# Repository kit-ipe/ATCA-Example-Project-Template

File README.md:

# ATCA Template

ATCA template containing multiple sub-projects.

## Project Folder structure

- fba_template "Full FBA" - Carrier Style with debugging with KRIA SoC and Carrier according to AMC.0 Spec.
- rtm_template "Full RTM" - RTM to be used with "Full Version"
- amc_template "AMC" - AMC to be used with "Full FBA" or "Carrier FBA"
- led_pcb: LED PCB to be used with every AMC Carier

- BOM: example BOM combination for one assemby of 1 Full FBA, 1 Full RTM and 1 LED PCB and 4 AMC

## Individual Project Folder structure

- sch/ -> to store sub schematic sheets
- mech -> to store dxf files used in mechanical tasks
- images -> to store images for the README or other purposes
- gerbers -> to store Gerber files

## Repositories

- [github](https://github.com/kit-ipe/ATCA-Example-Project-Template)

## Licensing

Copyright Luis Ardila, Carsten Schmerbeck 2023.

This source describes Open Hardware and is licensed under the CERN-OHL-P v2
You may redistribute and modify this documentation and make products
using it under the terms of the CERN-OHL-P v2 [https:/cern.ch/cern-ohl](https:/cern.ch/cern-ohl).
This documentation is distributed WITHOUT ANY EXPRESS OR IMPLIED
WARRANTY, INCLUDING OF MERCHANTABILITY, SATISFACTORY QUALITY
AND FITNESS FOR A PARTICULAR PURPOSE. Please see the CERN-OHL-P v2
for applicable conditions.

## Version History

- 30.11.2022 Initial version - Carsten Schmerbeck

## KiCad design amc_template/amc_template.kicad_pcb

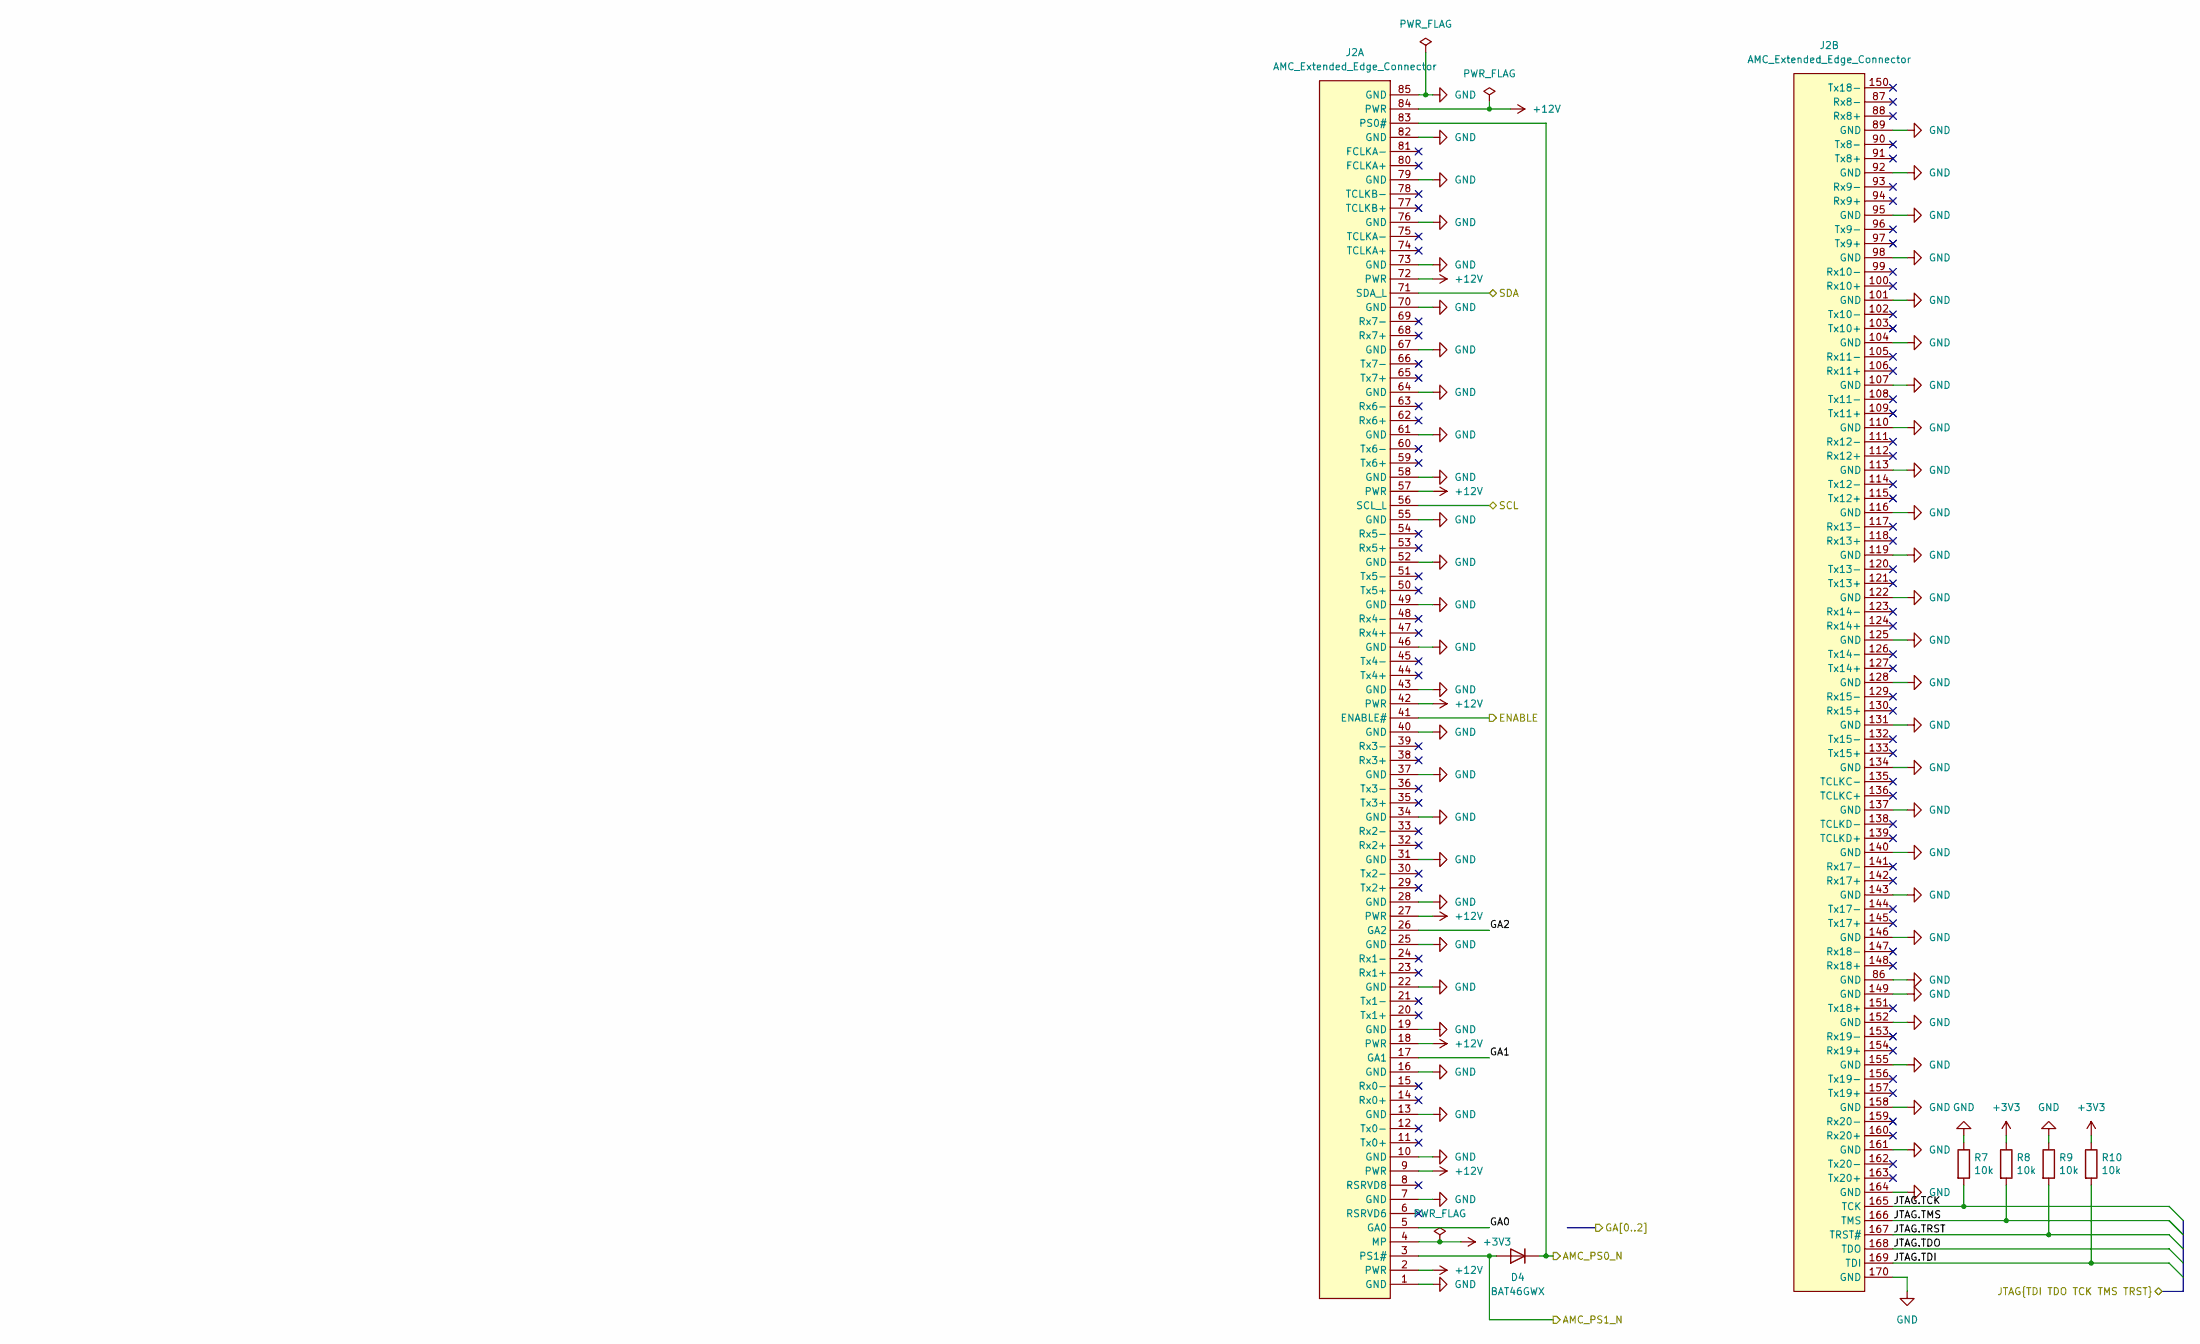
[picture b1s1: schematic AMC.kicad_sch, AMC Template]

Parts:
D4: BAT46GWX; D_SOD-123; mouser# 841-BAT46GWX
J2: AMC_Extended_Edge_Connector; AMC Card-edge
R7, R8, R9, R10: 10k; R_0402_1005Metric; digikey# A129639CT-ND

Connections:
+3V3: J2.4 (MP), R8.1, R10.1; also elsewhere on the board
+12V: J2.2 (PWR), J2.9 (PWR), J2.18 (PWR), J2.27 (PWR), J2.42 (PWR), J2.57 (PWR), J2.72 (PWR), J2.84 (PWR); also elsewhere on the board
/AMC_PS0_N: D4.1 (K), J2.83 (PS0#); also elsewhere on the board
/AMC_PS1_N: D4.2 (A), J2.3 (PS1#); also elsewhere on the board
/ENABLE: J2.41 (ENABLE#); also elsewhere on the board
/GA0: J2.5 (GA0); also elsewhere on the board
/GA1: J2.17 (GA1); also elsewhere on the board
/GA2: J2.26 (GA2); also elsewhere on the board
/JTAG.TCK: J2.165 (TCK), R7.2; also elsewhere on the board
/JTAG.TDI: J2.169 (TDI), R10.2; also elsewhere on the board
/JTAG.TDO: J2.168 (TDO); also elsewhere on the board
/JTAG.TMS: J2.166 (TMS), R8.2; also elsewhere on the board
/JTAG.TRST: J2.167 (TRST#), R9.2
/SCL: J2.56 (SCL_L); also elsewhere on the board
/SDA: J2.71 (SDA_L); also elsewhere on the board
GND: J2.1 (GND), J2.7 (GND), J2.10 (GND), J2.13 (GND), J2.16 (GND), J2.19 (GND), J2.22 (GND), J2.25 (GND), J2.28 (GND), J2.31 (GND), J2.34 (GND), J2.37 (GND), J2.40 (GND), J2.43 (GND), J2.46 (GND), J2.49 (GND), J2.52 (GND), J2.55 (GND), J2.58 (GND), J2.61 (GND), J2.64 (GND), J2.67 (GND), J2.70 (GND), J2.73 (GND), J2.76 (GND), J2.79 (GND), J2.82 (GND), J2.85 (GND), J2.86 (GND), J2.89 (GND), J2.92 (GND), J2.95 (GND), J2.98 (GND), J2.101 (GND), J2.104 (GND), J2.107 (GND), J2.110 (GND), J2.113 (GND), J2.116 (GND), J2.119 (GND), J2.122 (GND), J2.125 (GND), J2.128 (GND), J2.131 (GND), J2.134 (GND), J2.137 (GND), J2.140 (GND), J2.143 (GND), J2.146 (GND), J2.149 (GND), J2.152 (GND), J2.155 (GND), J2.158 (GND), J2.161 (GND), J2.164 (GND), J2.170 (GND), R7.1, R9.1; also elsewhere on the board

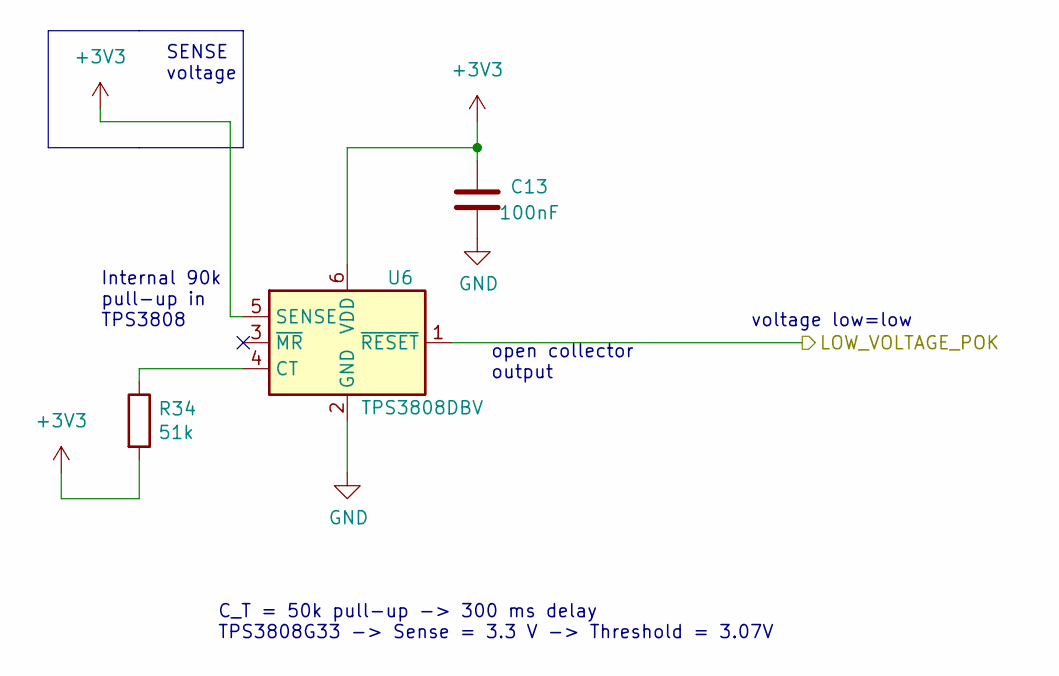
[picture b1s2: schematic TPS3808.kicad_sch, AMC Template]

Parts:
C13: 100nF; C_0402_1005Metric; voltage 25 V
R34: 51k; R_0402_1005Metric; digikey# RMCF0402FT51K0CT-ND
U6: TPS3808DBV; SOT-23-6; digikey# 296-37671-1-ND

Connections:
+3V3: C13.1, R34.2, U6.5 (SENSE), U6.6 (VDD); also elsewhere on the board
/MMC/LOW_VOLTAGE_POK: U6.1 (~RESET); also elsewhere on the board
GND: C13.2, U6.2 (GND); also elsewhere on the board
unnamed: R34.1, U6.4 (CT)

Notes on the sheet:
Internal 90k pull-up in TPS3808
C_T = 50k pull-up -> 300 ms delay TPS3808G33 -> Sense = 3.3 V -> Threshold = 3.07V
open collector output
SENSE voltage
voltage low=low

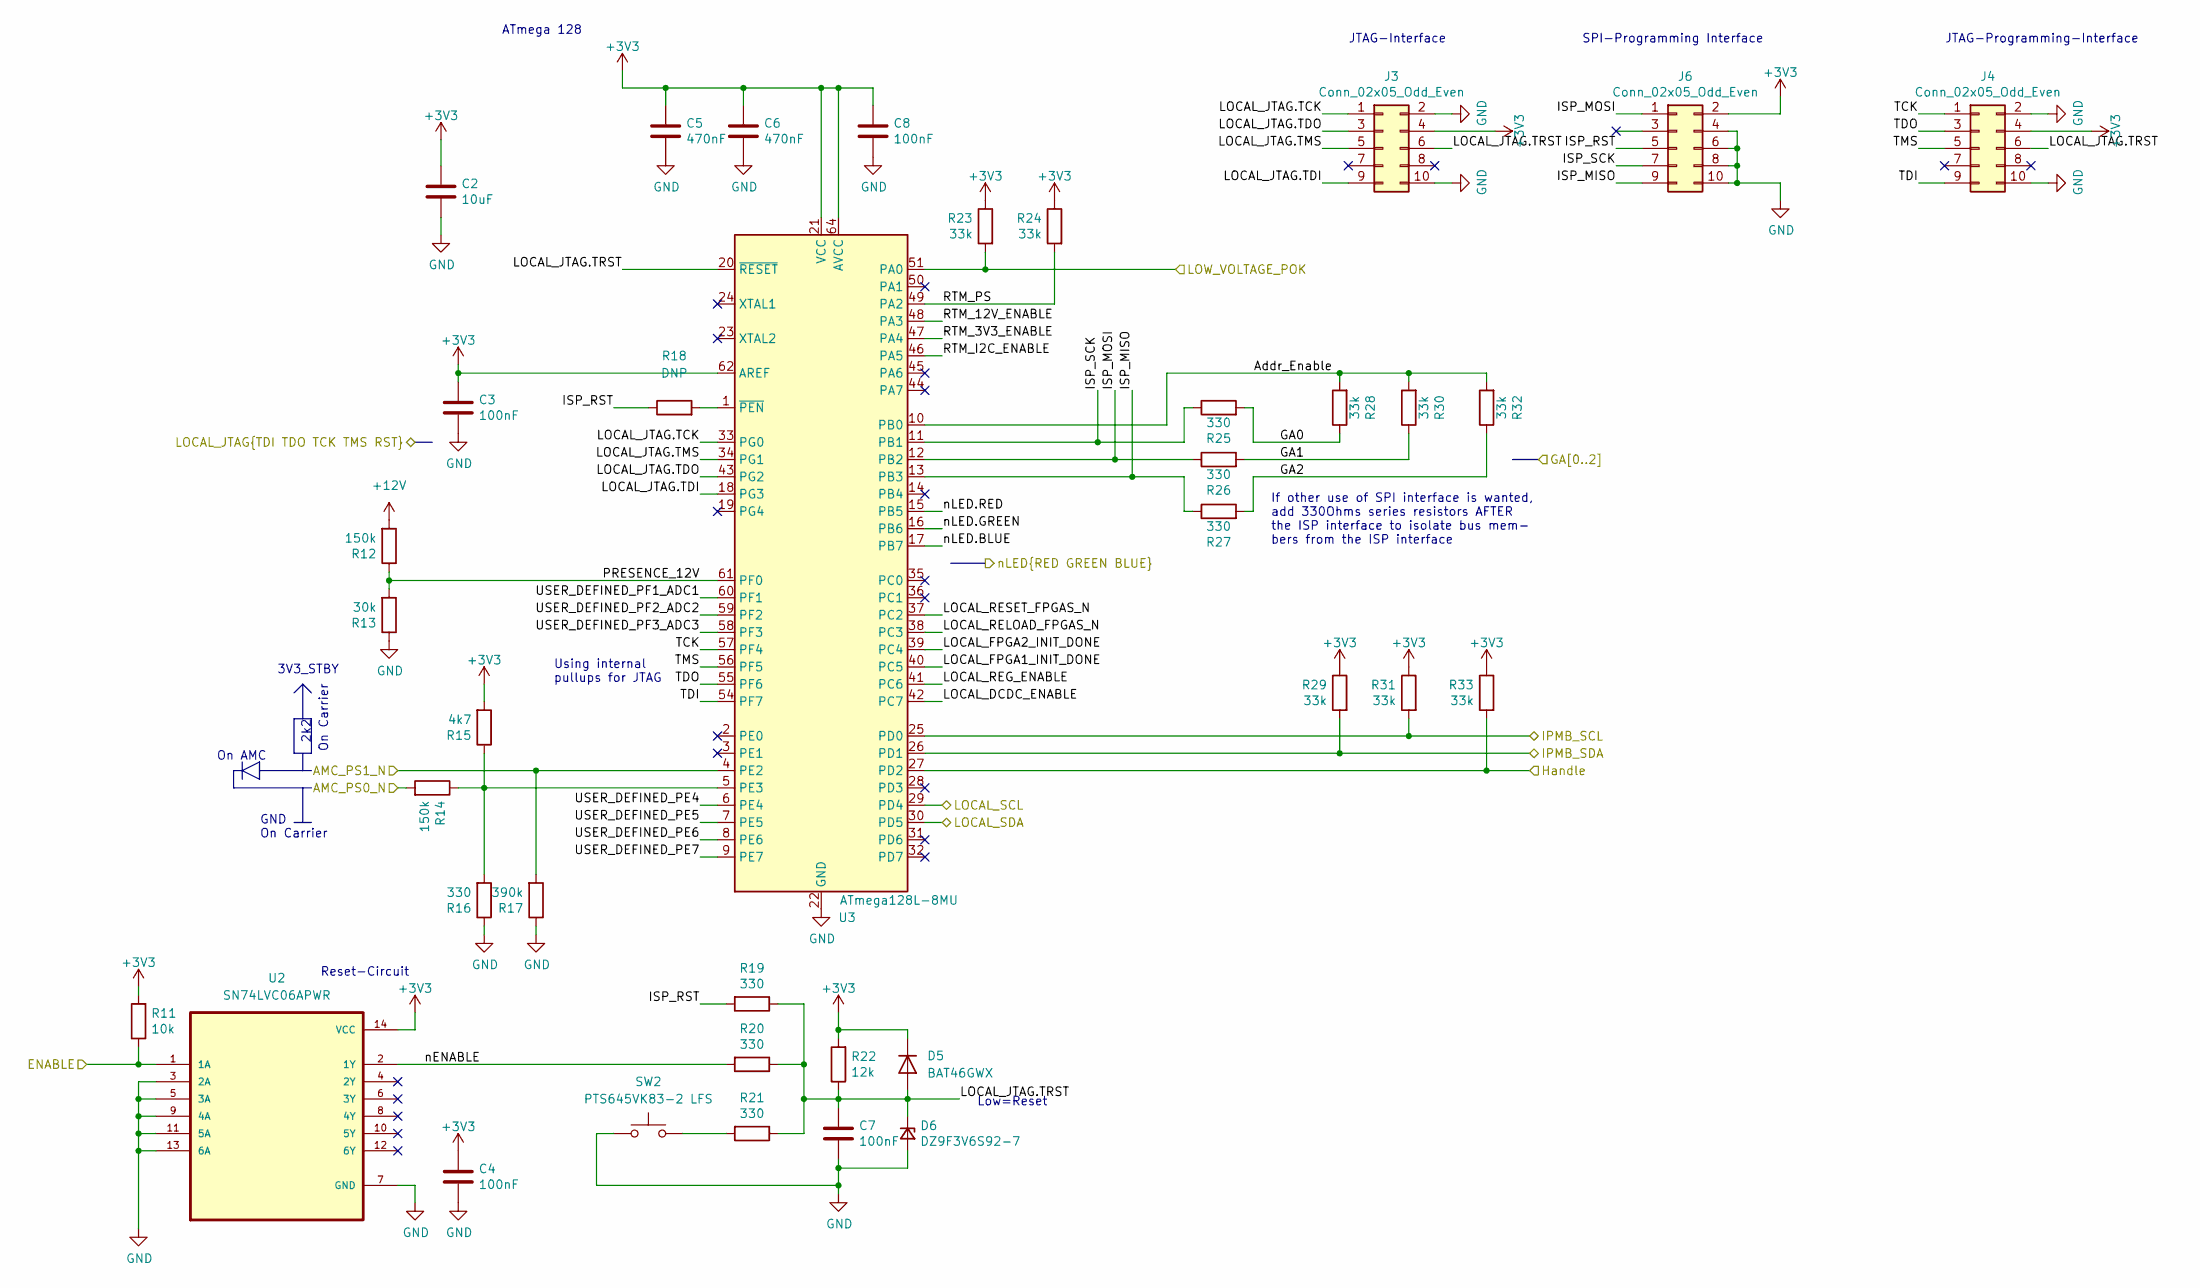
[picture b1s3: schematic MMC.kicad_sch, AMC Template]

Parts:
C2: 10uF; C_1210_3225Metric; digikey# 445-3942-1-ND
C3, C4, C7, C8: 100nF; C_0402_1005Metric
C5, C6: 470nF; C_0402_1005Metric
D5: BAT46GWX; D_SOD-123; mouser# 841-BAT46GWX
D6: DZ9F3V6S92-7; D_SOD-923; digikey# DZ9F3V6S92-7DICT-ND
J3, J4: Conn_02x05_Odd_Even; IDC-Header_2x05_P2.54mm_Horizontal_withoutsilkscreen; mouser# 571-5103311-1; digikey# A33180-ND
J6: Conn_02x05_Odd_Even; PinHeader_2x05_P2.54mm_Vertical
R11: 10k; R_0402_1005Metric; digikey# A129639CT-ND
R12, R14: 150k; R_0402_1005Metric
R13: 30k; R_0402_1005Metric
R15: 4k7; R_0402_1005Metric
R16, R19, R20, R21, R25, R26, R27: 330; R_0402_1005Metric
R17: 390k; R_0402_1005Metric
R18: DNP; R_0402_1005Metric
R22: 12k; R_0402_1005Metric; digikey# A129640CT-ND
R23, R24, R28, R29, R30, R31, R32, R33: 33k; R_0402_1005Metric
SW2: PTS645VK83-2 LFS; PTS645VK83-2; digikey# CKN10950-ND
U2: SN74LVC06APWR; TSSOP-14_4.4x5mm_P0.65mm
U3: ATmega128L-8MU; QFN-64-1EP_9x9mm_P0.5mm_EP5.4x5.4mm; mouser# 556-ATMEGA128L-8MUR; digikey# 2156-ATMEGA128L-8MU-ND

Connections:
+3V3: C2.1, C3.1, C4.1, C5.2, C6.1, C8.1, D5.1 (K), J3.4, J4.4, J6.2, R11.2, R15.2, R22.2, R23.1, R24.1, R29.1, R31.1, R33.1, U2.14 (VCC), U3.21 (VCC), U3.52 (VCC), U3.62 (AREF), U3.64 (AVCC); also elsewhere on the board
+12V: R12.2; also elsewhere on the board
/AMC_PS0_N: R14.2; also elsewhere on the board
/AMC_PS1_N: R17.2, U3.4 (PE2); also elsewhere on the board
/AT24C512C/SCL: U3.29 (PD4); also elsewhere on the board
/AT24C512C/SDA: U3.30 (PD5); also elsewhere on the board
/ENABLE: R11.1, U2.1 (1A); also elsewhere on the board
/GA0: R25.2, R28.1; also elsewhere on the board
/GA1: R26.2, R30.1; also elsewhere on the board
/GA2: R27.2, R32.1; also elsewhere on the board
/JTAG.TCK: J3.1, U3.33 (PG0); also elsewhere on the board
/JTAG.TDI: J3.9, U3.18 (PG3); also elsewhere on the board
/JTAG.TDO: J3.3, U3.43 (PG2); also elsewhere on the board
/JTAG.TMS: J3.5, U3.34 (PG1); also elsewhere on the board
/MMC/Addr_Enable: R28.2, R30.2, R32.2, U3.10 (PB0)
/MMC/Handle: R33.2, U3.27 (PD2); also elsewhere on the board
/MMC/ISP_MISO: J6.9, R27.1, U3.13 (PB3)
/MMC/ISP_MOSI: J6.1, R26.1, U3.12 (PB2)
/MMC/ISP_RST: J6.5, R18.1, R19.2
/MMC/ISP_SCK: J6.7, R25.1, U3.11 (PB1)
/MMC/LOCAL_DCDC_ENABLE: U3.42 (PC7)
/MMC/LOCAL_FPGA1_INIT_DONE: U3.40 (PC5)
/MMC/LOCAL_FPGA2_INIT_DONE: U3.39 (PC4)
/MMC/LOCAL_JTAG.TRST: C7.1, D5.2 (A), D6.1 (K), J3.6, J4.6, R19.1, R20.1, R21.1, R22.1, U3.20 (~RESET)
/MMC/LOCAL_REG_ENABLE: U3.41 (PC6)
/MMC/LOCAL_RELOAD_FPGAS_N: U3.38 (PC3)
/MMC/LOCAL_RESET_FPGAS_N: U3.37 (PC2)
/MMC/LOW_VOLTAGE_POK: R23.2, U3.51 (PA0); also elsewhere on the board
/MMC/PRESENCE_12V: R12.1, R13.2, U3.61 (PF0)
/MMC/RTM_3V3_ENABLE: U3.47 (PA4)
/MMC/RTM_12V_ENABLE: U3.48 (PA3)
/MMC/RTM_I2C_ENABLE: U3.46 (PA5)
/MMC/RTM_PS: R24.2, U3.49 (PA2)
/MMC/TCK: J4.1, U3.57 (PF4)
/MMC/TDI: J4.9, U3.54 (PF7)
/MMC/TDO: J4.3, U3.55 (PF6)
/MMC/TMS: J4.5, U3.56 (PF5)
/MMC/USER_DEFINED_PE4: U3.6 (PE4)
/MMC/USER_DEFINED_PE5: U3.7 (PE5)
/MMC/USER_DEFINED_PE6: U3.8 (PE6)
/MMC/USER_DEFINED_PE7: U3.9 (PE7)
/MMC/USER_DEFINED_PF1_ADC1: U3.60 (PF1)
/MMC/USER_DEFINED_PF2_ADC2: U3.59 (PF2)
/MMC/USER_DEFINED_PF3_ADC3: U3.58 (PF3)
/MMC/nENABLE: R20.2, U2.2 (1Y)
/MMC/nLED.BLUE: U3.17 (PB7); also elsewhere on the board
/MMC/nLED.GREEN: U3.16 (PB6); also elsewhere on the board
/MMC/nLED.RED: U3.15 (PB5); also elsewhere on the board
/SCL: R31.2, U3.25 (PD0); also elsewhere on the board
/SDA: R29.2, U3.26 (PD1); also elsewhere on the board
GND: C2.2, C3.2, C4.2, C5.1, C6.2, C7.2, C8.2, D6.2 (A), J3.2, J3.10, J4.2, J4.10, J6.4, J6.6, J6.8, J6.10, R13.1, R16.1, R17.1, SW2.1, U2.3 (2A), U2.5 (3A), U2.7 (GND), U2.9 (4A), U2.11 (5A), U2.13 (6A), U3.22 (GND), U3.53 (GND), U3.63 (GND), U3.65 (GND); also elsewhere on the board
unnamed: R14.1, R15.1, R16.2, U3.5 (PE3)
unnamed: R18.2, U3.1 (~PEN)
unnamed: R21.2, SW2.2

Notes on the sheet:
Low=Reset
If other use of SPI interface is wanted, add 330Ohms series resistors AFTER the ISP interface to isolate bus mem- bers from the ISP interface
On Carrier
GND On Carrier
Reset-Circuit
ATmega 128
JTAG-Programming-Interface
SPI-Programming Interface
Using internal pullups for JTAG
On AMC
2k2
JTAG-Interface
3V3_STBY

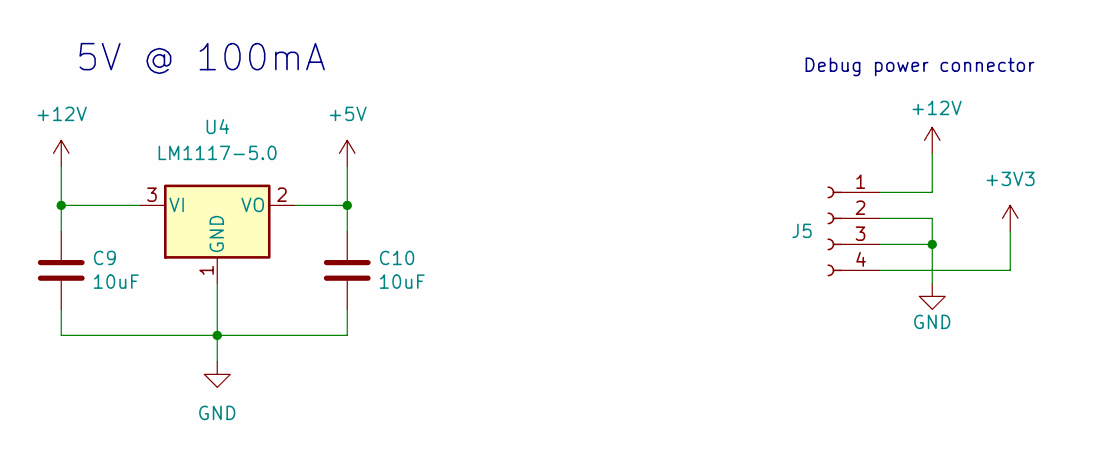
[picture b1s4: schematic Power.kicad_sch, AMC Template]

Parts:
C9, C10: 10uF; C_1210_3225Metric; digikey# 445-3942-1-ND
J5: Conn_3V3_EXT; PinHeader-4_P3.5mm
U4: LM1117-5.0; SOT-223-3_TabPin2; mouser# 863-LM1117MPX-50NOPB

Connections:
+3V3: J5.4; also elsewhere on the board
+5V: C10.1, U4.2 (VO); also elsewhere on the board
+12V: C9.1, J5.1, U4.3 (VI); also elsewhere on the board
GND: C9.2, C10.2, J5.2, J5.3, U4.1 (GND); also elsewhere on the board

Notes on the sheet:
Debug power connector
5V @ 100mA

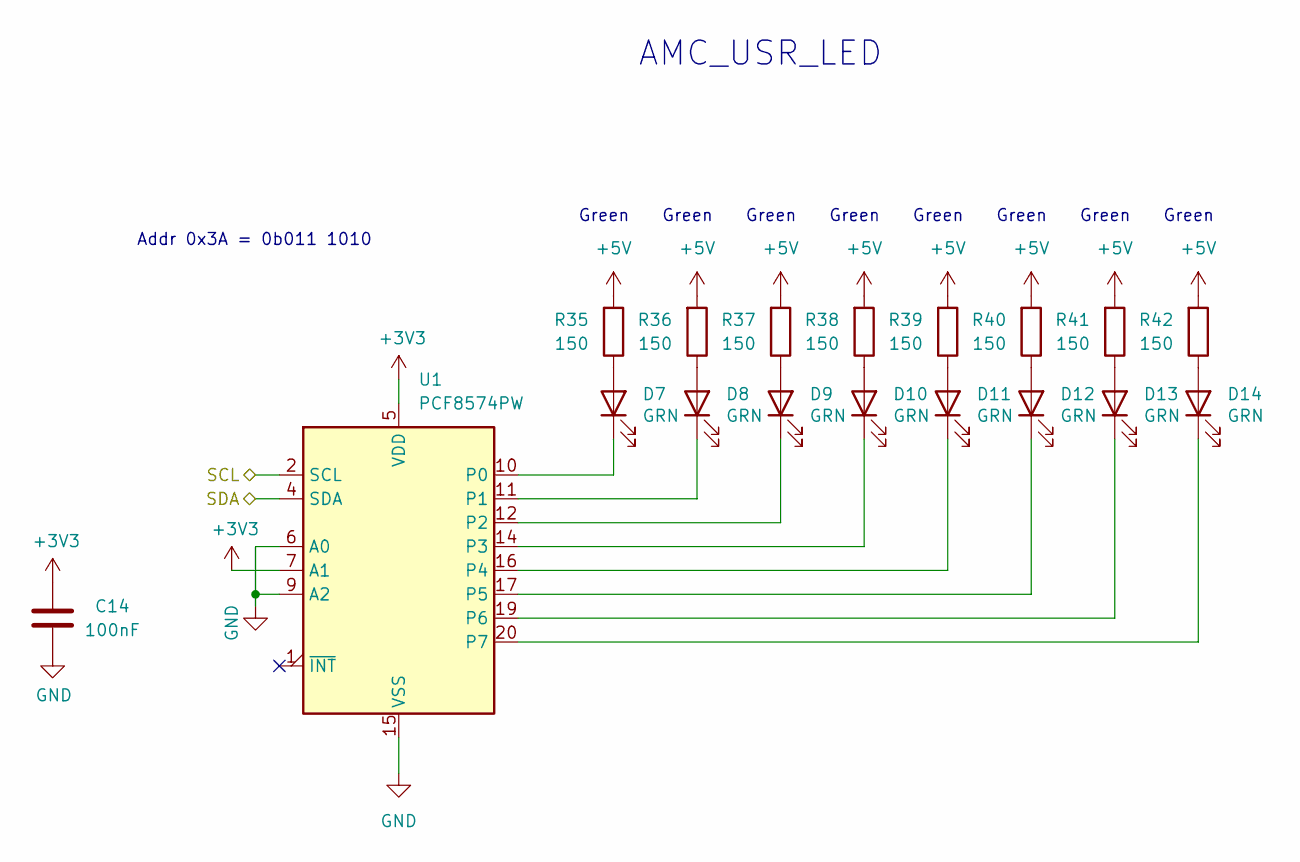
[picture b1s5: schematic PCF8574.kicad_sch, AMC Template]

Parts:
C14: 100nF; C_0402_1005Metric
D7, D8, D9, D10, D11, D12, D13, D14: GRN; APA2106x; digikey# 754-1057-1-ND
R35, R36, R37, R38, R39, R40, R41, R42: 150; R_0402_1005Metric; digikey# A12961CT-ND
U1: PCF8574PW; TSSOP-20_4.4x6.5mm_P0.65mm; mouser# 595-PCF8574PW

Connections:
+3V3: C14.1, U1.5 (VDD), U1.7 (A1); also elsewhere on the board
+5V: R35.2, R36.2, R37.2, R38.2, R39.2, R40.2, R41.2, R42.2; also elsewhere on the board
/AT24C512C/SCL: U1.2 (SCL); also elsewhere on the board
/AT24C512C/SDA: U1.4 (SDA); also elsewhere on the board
GND: C14.2, U1.6 (A0), U1.9 (A2), U1.15 (VSS); also elsewhere on the board
unnamed: D7.1 (K), U1.10 (P0)
unnamed: D7.2 (A), R35.1
unnamed: D8.1 (K), U1.11 (P1)
unnamed: D8.2 (A), R36.1
unnamed: D9.1 (K), U1.12 (P2)
unnamed: D9.2 (A), R37.1
unnamed: D10.1 (K), U1.14 (P3)
unnamed: D10.2 (A), R38.1
unnamed: D11.1 (K), U1.16 (P4)
unnamed: D11.2 (A), R39.1
unnamed: D12.1 (K), U1.17 (P5)
unnamed: D12.2 (A), R40.1
unnamed: D13.1 (K), U1.19 (P6)
unnamed: D13.2 (A), R41.1
unnamed: D14.1 (K), U1.20 (P7)
unnamed: D14.2 (A), R42.1

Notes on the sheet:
Green
Addr 0x3A = 0b011 1010
AMC_USR_LED

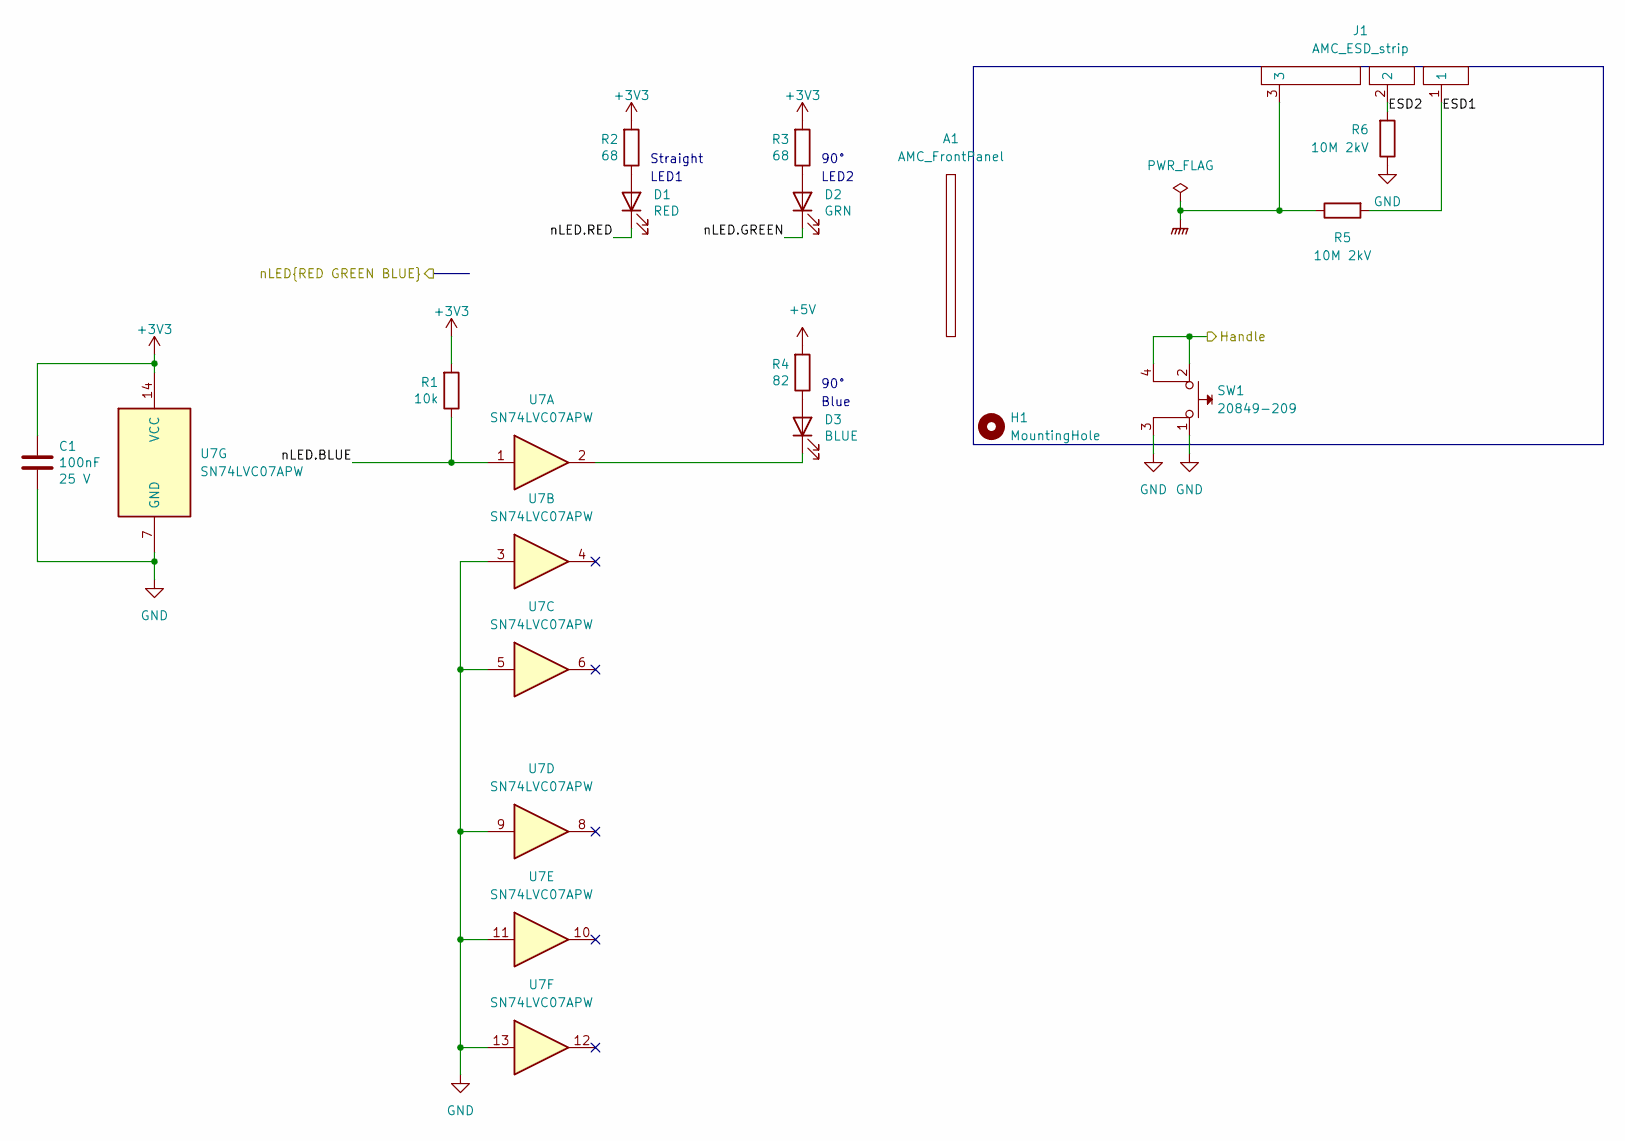
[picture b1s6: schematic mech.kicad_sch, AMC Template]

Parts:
A1: AMC_FrontPanel; 20849-270
C1: 100nF; C_0402_1005Metric; voltage 25 V
D1: RED; LED_0805_2012Metric; mouser# 604-AP2012EC
D2: GRN; APA1606x; digikey# 754-1051-1-ND
D3: BLUE; APA1606x; digikey# 754-1424-1-ND
H1: MountingHole; MountingHole_2.7mm
J1: AMC_ESD_strip
R1: 10k; R_0402_1005Metric; digikey# A129639CT-ND
R2, R3: 68; R_0402_1005Metric; digikey# A129613CT-ND
R4: 82; R_0402_1005Metric; digikey# A129614CT-ND
R5, R6: 10M 2kV; R_2010_5025Metric; digikey# 118-CHV2010-FX-1005ESTCT-ND
SW1: 20849-209
U7: SN74LVC07APW; TSSOP-14_4.4x5mm_P0.65mm; digikey# 296-26575-5-ND

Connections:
+3V3: C1.1, R1.2, R2.2, R3.2, U7.14 (VCC); also elsewhere on the board
+5V: R4.2; also elsewhere on the board
/MMC/Handle: SW1.2, SW1.4; also elsewhere on the board
/MMC/nLED.BLUE: R1.1, U7.1; also elsewhere on the board
/MMC/nLED.GREEN: D2.1 (K); also elsewhere on the board
/MMC/nLED.RED: D1.1 (K); also elsewhere on the board
/mech/ESD1: J1.1, R5.2
/mech/ESD2: J1.2, R6.2
GND: C1.2, R6.1, SW1.1, SW1.3, U7.3, U7.5, U7.7 (GND), U7.9, U7.11, U7.13; also elsewhere on the board
GNDPWR: J1.3, R5.1
unnamed: D1.2 (A), R2.1
unnamed: D2.2 (A), R3.1
unnamed: D3.1 (K), U7.2
unnamed: D3.2 (A), R4.1

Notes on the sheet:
LED2
Blue
LED1
90°
Straight

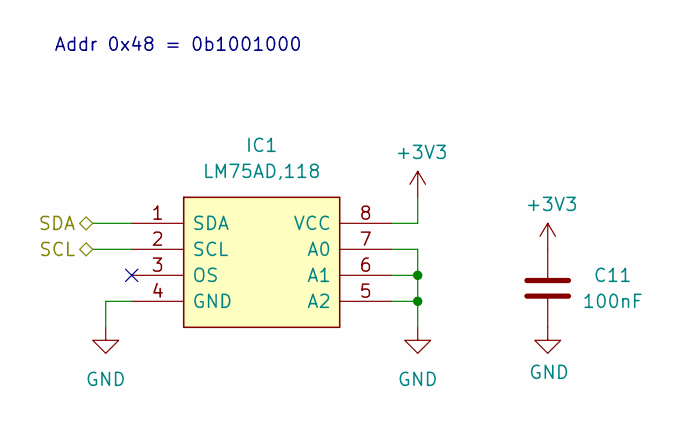
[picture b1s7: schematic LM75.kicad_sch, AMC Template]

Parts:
C11: 100nF; C_0402_1005Metric
IC1: LM75AD,118; SO-8_3.9x4.9mm_P1.27mm; mouser# 771-LM75AD-T

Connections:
+3V3: C11.1, IC1.8 (VCC); also elsewhere on the board
/AT24C512C/SCL: IC1.2 (SCL); also elsewhere on the board
/AT24C512C/SDA: IC1.1 (SDA); also elsewhere on the board
GND: C11.2, IC1.4 (GND), IC1.5 (A2), IC1.6 (A1), IC1.7 (A0); also elsewhere on the board

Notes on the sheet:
Addr 0x48 = 0b1001000

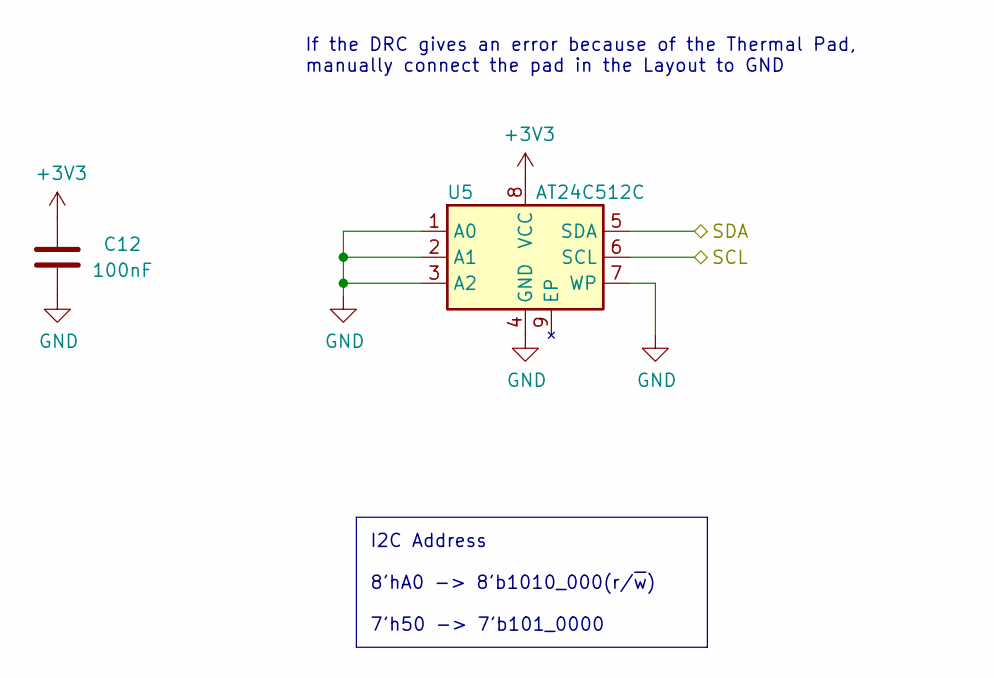
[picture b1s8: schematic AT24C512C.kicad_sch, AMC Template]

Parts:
C12: 100nF; C_0402_1005Metric
U5: AT24C512C; DFN-8-1EP_3x2mm_P0.5mm_EP1.3x1.5mm; digikey# AT24C512C-MAHM-TCT-ND

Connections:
+3V3: C12.1, U5.8 (VCC); also elsewhere on the board
/AT24C512C/SCL: U5.6 (SCL); also elsewhere on the board
/AT24C512C/SDA: U5.5 (SDA); also elsewhere on the board
GND: C12.2, U5.1 (A0), U5.2 (A1), U5.3 (A2), U5.4 (GND), U5.7 (WP); also elsewhere on the board

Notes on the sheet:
I2C Address 8'hA0 -> 8'b1010_000(r/~{w}) 7'h50 -> 7'b101_0000
If the DRC gives an error because of the Thermal Pad, manually connect the pad in the Layout to GND

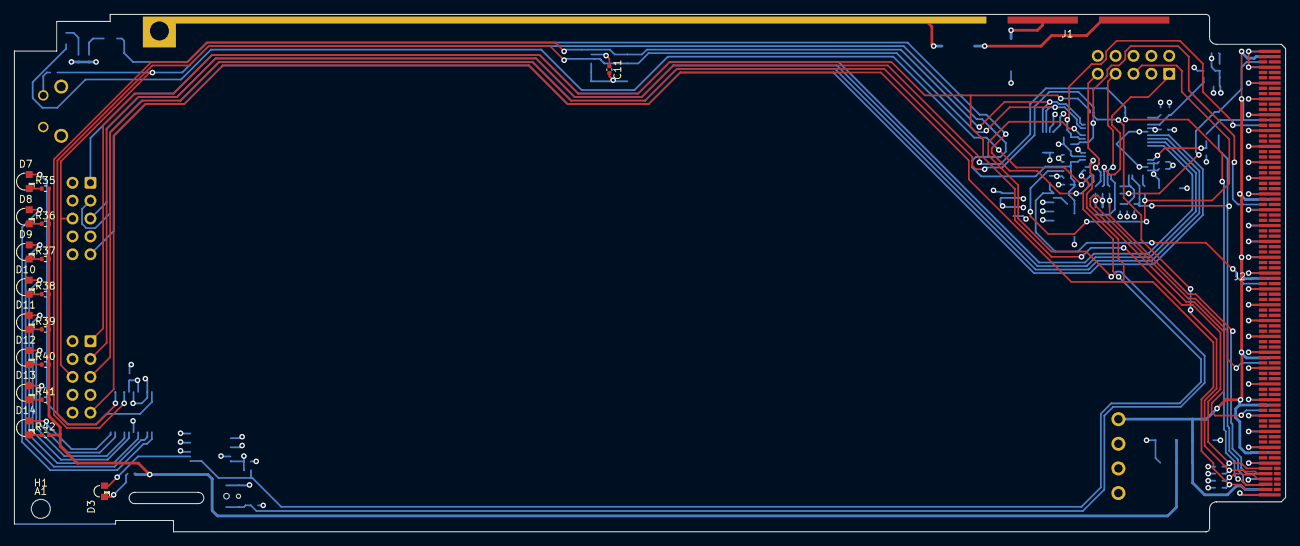
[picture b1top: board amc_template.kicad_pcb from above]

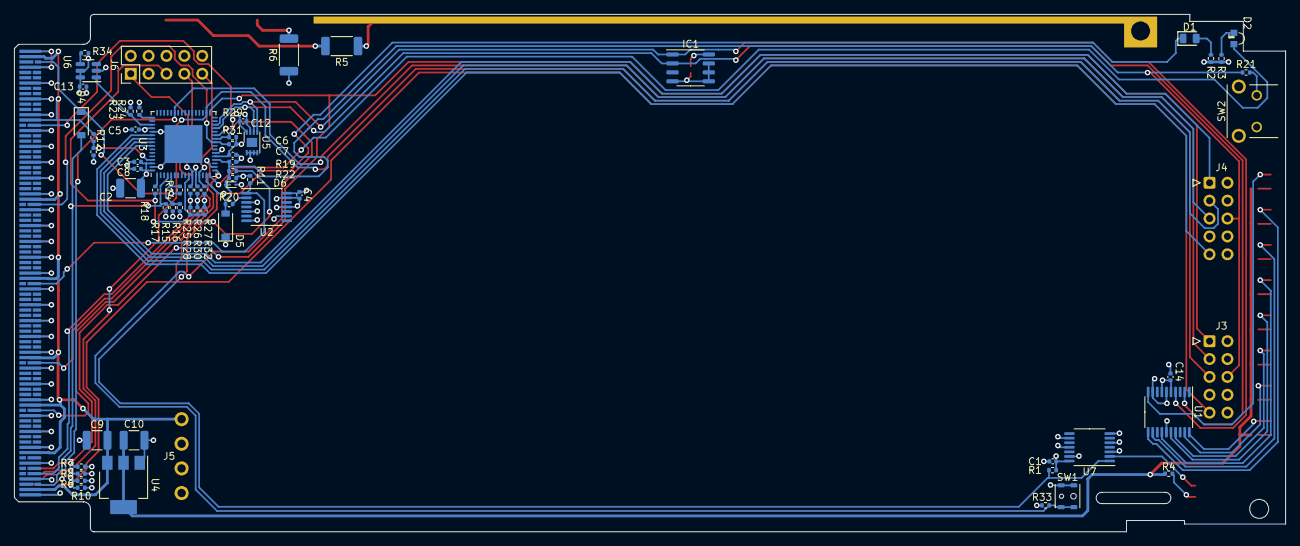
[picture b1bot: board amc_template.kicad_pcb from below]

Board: 4 copper layers, 180.6 x 73.5 mm, 88 parts (66 on the bottom side), 64 nets.

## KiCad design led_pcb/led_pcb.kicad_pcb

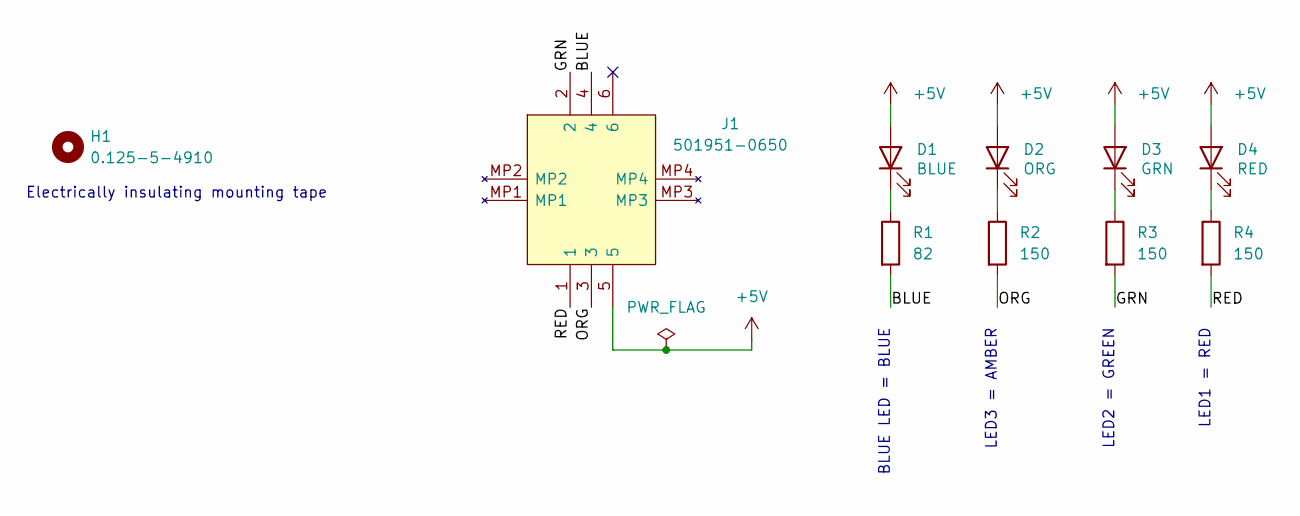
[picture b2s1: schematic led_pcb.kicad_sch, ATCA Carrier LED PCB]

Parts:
D1: BLUE; APA1606x; digikey# 754-1424-1-ND
D2: ORG; APA1606x; digikey# 754-1053-1-ND
D3: GRN; APA1606x; digikey# 754-1051-1-ND
D4: RED; APA1606x; digikey# 754-1054-1-ND
H1: 0.125-5-4910; digikey# 3M156589-ND
J1: 501951-0650; 50195106501; mouser# 538-501951-0650
R1: 82; R_0402_1005Metric; digikey# A129614CT-ND
R2, R3, R4: 150; R_0402_1005Metric; digikey# A129617CT-ND

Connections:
+5V: D1.2 (A), D2.2 (A), D3.2 (A), D4.2 (A), J1.5
/BLUE: J1.4, R1.2
/GRN: J1.2, R3.2
/ORG: J1.3, R2.2
/RED: J1.1, R4.2
unnamed: D1.1 (K), R1.1
unnamed: D2.1 (K), R2.1
unnamed: D3.1 (K), R3.1
unnamed: D4.1 (K), R4.1

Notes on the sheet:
Electrically insulating mounting tape
LED2 = GREEN
LED1 = RED
BLUE LED = BLUE
LED3 = AMBER

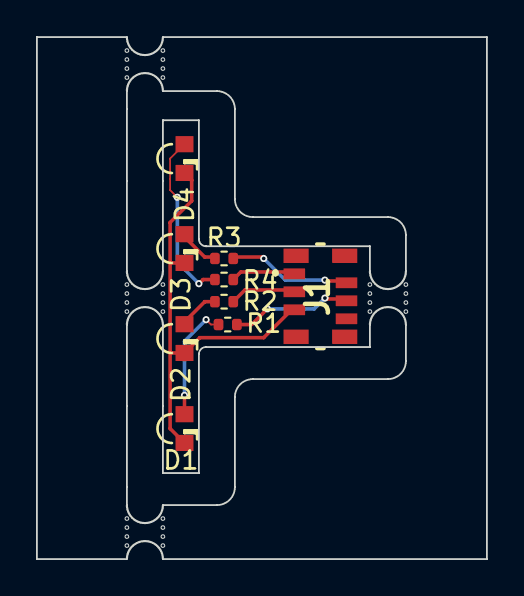
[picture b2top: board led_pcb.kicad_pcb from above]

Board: 2 copper layers, 25.0 x 29.0 mm, 10 parts (1 on the bottom side), 9 nets.

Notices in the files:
amc_template/amc_template.kicad_pcb:
Licensed under CERN-OHL-P v2
